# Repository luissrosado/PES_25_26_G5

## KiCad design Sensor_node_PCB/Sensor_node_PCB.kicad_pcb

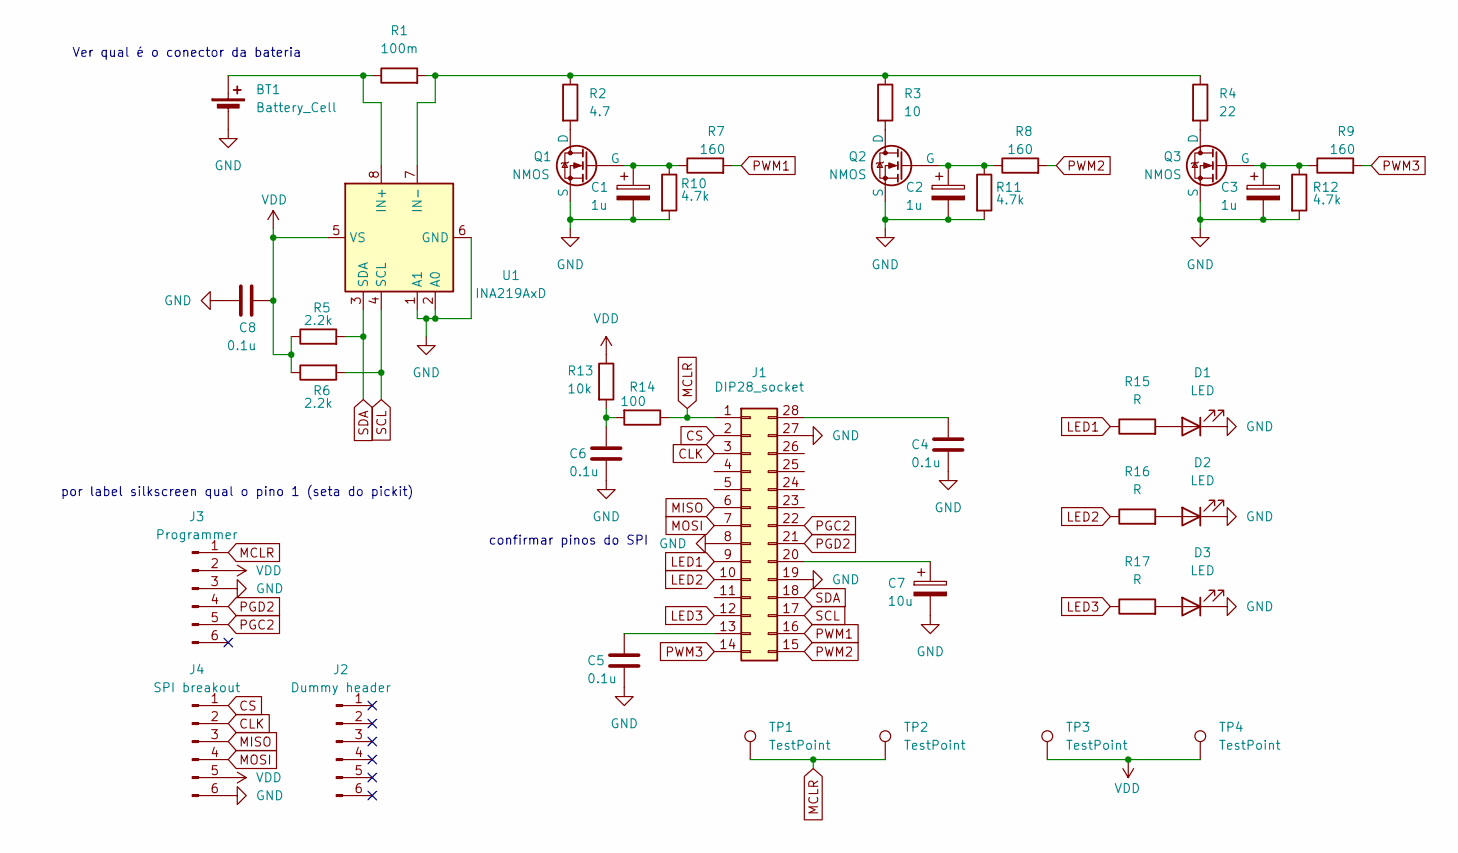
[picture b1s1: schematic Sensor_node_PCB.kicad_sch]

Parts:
BT1: Battery_Cell; PinHeader_1x02_P2.00mm_Vertical
C1, C2, C3: 1u; CP_Radial_D5.0mm_P2.00mm
C4, C5, C6, C8: 0.1u; C_Rect_L7.0mm_W3.5mm_P5.00mm
C7: 10u; CP_Radial_D5.0mm_P2.00mm
D1, D2, D3: LED; LED_D4.0mm
J1: DIP28_socket; DIP-28_W7.62mm_Socket
J2: Dummy header; PinHeader_1x06_P2.54mm_Vertical
J3: Programmer; PinHeader_1x06_P2.54mm_Vertical
J4: SPI breakout; PinHeader_1x06_P2.54mm_Vertical
Q1, Q2, Q3: NMOS; TO-220-3_Vertical
R1: 100m; C_1206_3216Metric_Pad1.33x1.80mm_HandSolder
R2: 4.7; R_Axial_Power_L38.0mm_W9.0mm_P45.72mm
R3: 10; R_Axial_Power_L50.0mm_W9.0mm_P55.88mm
R4: 22; R_Axial_Power_L50.0mm_W9.0mm_P55.88mm
R5, R6: 2.2k; R_Axial_DIN0309_L9.0mm_D3.2mm_P12.70mm_Horizontal
R7, R8, R9: 160; R_Axial_DIN0309_L9.0mm_D3.2mm_P12.70mm_Horizontal
R10, R11, R12: 4.7k; R_Axial_DIN0309_L9.0mm_D3.2mm_P12.70mm_Horizontal
R13: 10k; R_Axial_DIN0309_L9.0mm_D3.2mm_P12.70mm_Horizontal
R14: 100; R_Axial_DIN0309_L9.0mm_D3.2mm_P12.70mm_Horizontal
R15, R16, R17: R; R_Axial_DIN0309_L9.0mm_D3.2mm_P12.70mm_Horizontal
TP1, TP2, TP3, TP4: TestPoint; TestPoint_THTPad_1.5x1.5mm_Drill0.7mm
U1: INA219AxD; SOIC-8_3.9x4.9mm_P1.27mm

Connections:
CLK: J1.3, J4.2
CS: J1.2, J4.1
GND: BT1.2 (-), C1.2, C2.2, C3.2, C4.2, C5.2, C6.2, C7.2, C8.1, D1.1 (K), D2.1 (K), D3.1 (K), J1.8, J1.19, J1.27, J3.3, J4.6, Q1.3 (S), Q2.3 (S), Q3.3 (S), R10.2, R11.2, R12.2, U1.1 (A1), U1.2 (A0), U1.6 (GND)
LED1: J1.9, R15.1
LED2: J1.10, R16.1
LED3: J1.12, R17.1
MCLR: J1.1, J3.1, R14.1, TP1.1, TP2.1
MISO: J1.6, J4.3
MOSI: J1.7, J4.4
unnamed: BT1.1 (+), R1.1, U1.8 (IN+)
unnamed: C6.1, R13.2, R14.2
unnamed: D1.2 (A), R15.2
unnamed: D2.2 (A), R16.2
unnamed: D3.2 (A), R17.2
unnamed: C5.1, J1.13
unnamed: C7.1, J1.20
unnamed: C4.1, J1.28
unnamed: Q1.1 (D), R2.2
unnamed: C1.1, Q1.2 (G), R7.1, R10.1
unnamed: Q2.1 (D), R3.2
unnamed: C2.1, Q2.2 (G), R8.1, R11.1
unnamed: Q3.1 (D), R4.2
unnamed: C3.1, Q3.2 (G), R9.1, R12.1
unnamed: R1.2, R2.1, R3.1, R4.1, U1.7 (IN-)
PGC2: J1.22, J3.5
PGD2: J1.21, J3.4
PWM1: J1.16, R7.2
PWM2: J1.15, R8.2
PWM3: J1.14, R9.2
SCL: J1.17, R6.2, U1.4 (SCL)
SDA: J1.18, R5.2, U1.3 (SDA)
VDD: C8.2, J3.2, J4.5, R5.1, R6.1, R13.1, TP3.1, TP4.1, U1.5 (VS)

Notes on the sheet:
por label silkscreen qual o pino 1 (seta do pickit)
Ver qual é o conector da bateria
confirmar pinos do SPI

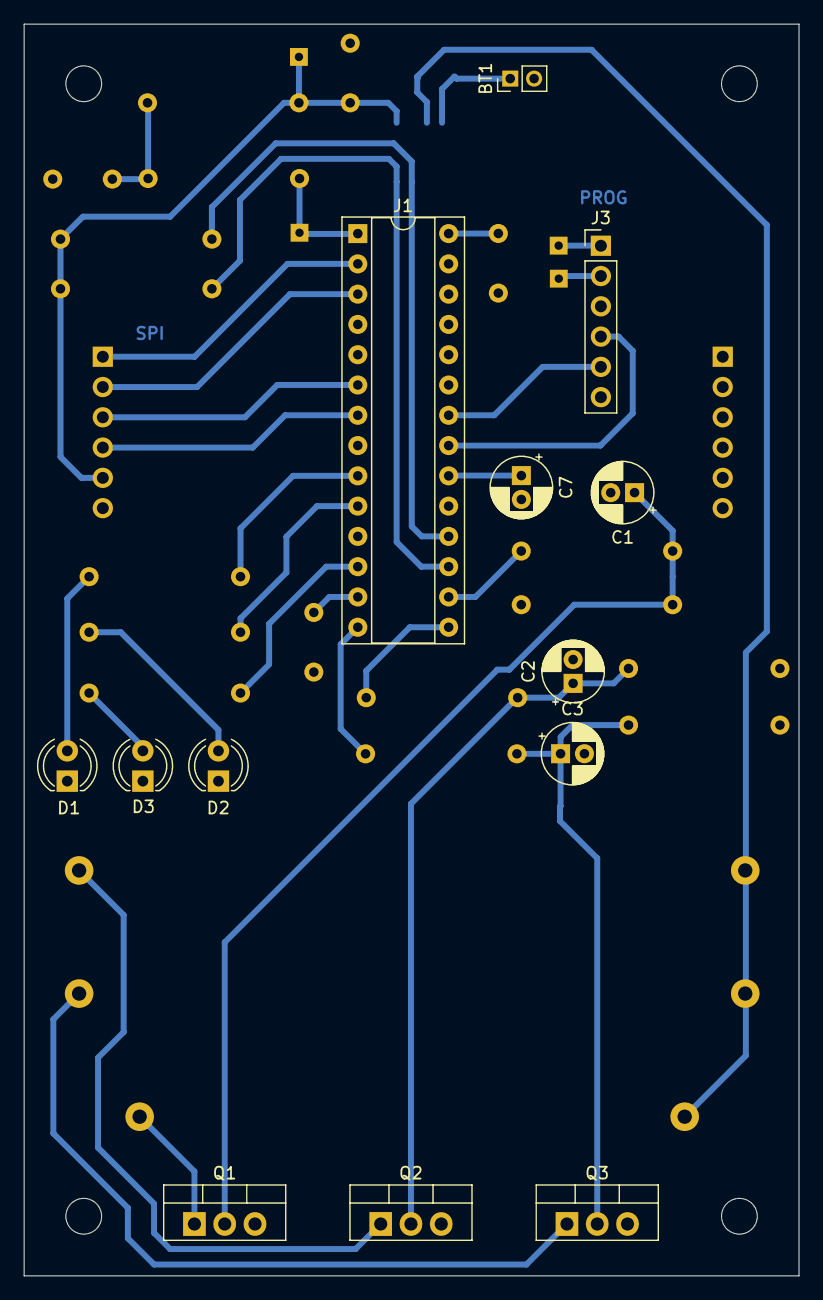
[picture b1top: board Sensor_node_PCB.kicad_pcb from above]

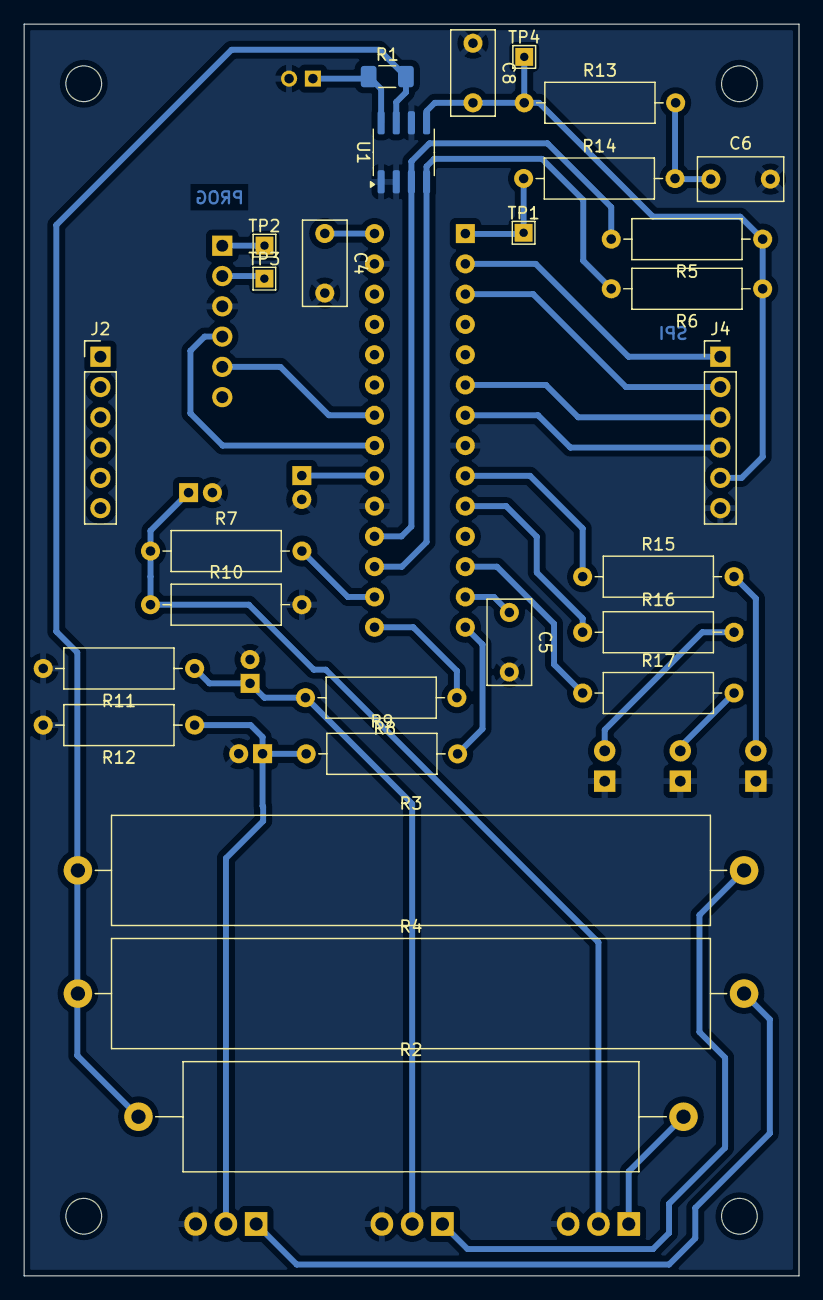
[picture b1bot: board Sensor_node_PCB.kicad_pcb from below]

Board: 2 copper layers, 65.0 x 105.0 mm, 41 parts (28 on the bottom side), 32 nets.

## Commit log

2025-09-12 I2C
    primeira tentativa de comunicação com o i2c
2025-09-14 I2C Tx code draft
    Could not test as pickit5 doesn't support mplab v5.3. As a solution either use a pickit3 instead or install a more recent version of mplab.
2025-09-15 I2C INA reading
    Code for reading INA measurements. Project builds successfully but has not been tested (need oscilloscope). Currently not using I2C interrupts.
    INA calibration code has to be written before trying to read power or current values.
2025-09-16 I2C INA calibration
2025-09-18 I2C improvements
    I2C_init corrected.
    I2C_Calibrate_INA seems to send correct information (testing with INA connected need to be performed).
    I2C_Read_INA has not been tested but follows a similar structure and therefore should also work (testing needs to be done both with and without INA).
2025-09-18 spi code
    spi code for pic24fj1024gb610
    need confirmation in lab
2025-09-19 PWM Signal Generation
    - Code for single PWM channel;
    - Documented;
    - To be tried out at today's lab;
    - To be further improved: add multiple channels, code written into functions;
2025-09-19 spi com confirmacao
    funciona com clock no osciloscopio
2025-09-19 First version of sensor node schematic
    Missing footprints and uC connections
2025-09-19 spi_slave
    start of the code for slave for sensor node
2025-09-20 PWM working (sort of)
    - PWM working with dedicated timers;
    - To do: check waveform on oscilloscope; find out why it stops; reorganize the code and put it into funtions;
2025-09-21 (Updated) Actual functioning version
2025-09-22 Timer1 wake-up
    Code for waking CPU from IDLE mode periodically using timer1 interrupt. When it wakes up, a pin is toggled which should be connected to an LED in order to check the code is working. Compiles but need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
2025-09-22 Timer reset
    Forgot to reset timer count. Now it is correct.
2025-09-23 PWM update (not quite there yet)
    - some problem with the duty cycle;
2025-09-24 Output Compare PWM module
    - working, functions created, safeguards to PPS pins created;
    - 2-do: add multiple modules and make them work simultaneously and use DMA to control PWM;
2025-09-24 Timer works
    Timer code has been tested and works.
2025-09-24 PWM ready for multiple channels
    - Pins need to be assigned the specific PPS function;
    - 2-Do: Output Compare with DMA;
2025-09-24 Revert "Merge branch 'main' of https://github.com/luissrosado/PES_25_26_G5"
    This reverts commit e8ca569d0b1d5ddb3494a55b4376186d325189a8, reversing
    changes made to 443614e28be1e8a0669e18b51373a44bc0f4c732.
2025-09-24 spi master
2025-09-25 spi slave
    precisa de ser testado
2025-09-25 spi slave
    testar comunicação miso
2025-09-26 spi introducao LED
2025-09-26 adicao de spi slave com lcd
2025-09-26 I2C working
2025-09-28 spi slave
2025-09-28 GUI start
2025-09-29 spi slave
    falta testar o miso não parece estar a comunicar
2025-10-01 spi_slave
    já temos comunicação master slave
2025-10-01 3 channels of PWM - testing
2025-10-01 criação do ficheiro projeto
2025-10-01 projeto
    i2c e spi integrados
    falta intergrar wake timer e pwm
2025-10-01 spi master
    update para permitir 3 mensagens
2025-10-01 spi master com ecra
2025-10-01 Node pcb schematic update
2025-10-02 Sensor Node Project Setup
    Integração
2025-10-02 PCB schematic updates
2025-10-02 PWM channel testing
2025-10-02 PCB layout started
2025-10-03 project file fix attempt
2025-10-03 sensor node project corrected
2025-10-03 spi master edit
2025-10-03 versao entrega intermédia
2025-10-03 tentativa spi com varias mensagens
2025-10-04 spi com varias mensagens
    funciona com mensagens predefinidas
2025-10-06 revert para entrega intermedia
2025-10-06 serial init
    criacao da funcao de init do serial ja com algumas configuracoes
2025-10-06 mensagens uart para serial
    organizacao das mensagens do uart para depender da gui para enviar o spi
2025-10-06 dummy byte
    acrescento de mensagem para corrigir problema de dummybyte
2025-10-06 organizacao das mensagens spi
    introducao no slave da organizacao das mensagens para o master
2025-10-06 PCB corrections and improvements
2025-10-08 uart funcional
2025-10-08 GUI developments
    - 2-Do: try COM port, try to send data, try to receive data;
    (try out the basic functionalities)
2025-10-08 PCB layout redone as shield for devboard
2025-10-10 controller
2025-10-10 PCB redone according to fabrication specs
